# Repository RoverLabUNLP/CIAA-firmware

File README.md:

# EDU-CIAA-NXP con VS Code

Proyecto C para la EDU-CIAA-NXP (LPC4337, Cortex-M4), con sAPI y FreeRTOS.
Reutiliza GCC ARM 8.2.1 y las bibliotecas de CIAA Software 1.1 instalados
en este equipo. No requiere abrir Eclipse.

## Compilar

1. Abrir esta carpeta en VS Code.
2. Instalar la extensión recomendada **C/C++ de Microsoft**.
3. Comenzar por `app/src/main.c` y seguir la [guía de la aplicación RTOS](app/README.md).
4. Presionar **Ctrl+Shift+B** para ejecutar **CIAA: compilar**.

También se puede ejecutar `make` en la terminal de esta carpeta.
El esquema crea seis tareas. La tarea de estado alterna LEDB cada 500 ms;
las mediciones permanecen inválidas y las salidas propuestas en cero.
No se acciona ningún motor ni se reciben comandos UART todavía.
La salida está en `app/out/app.elf`
y `app/out/app.bin`. Los errores aparecen en el panel Problemas.
Para eliminar los resultados: `make clean` o la tarea **CIAA: limpiar**.

Compilar comprueba sintaxis y enlace con las bibliotecas de la placa.
Para comprobar LEDs, entradas, comunicaciones y tiempos hay que cargar el
programa en la EDU-CIAA y probarlo allí. Esta configuración no simula la placa.

## Herramientas y bibliotecas

Se usa `$HOME/CIAA_Software_1.1-linux-x64`. Para otra ubicación:

```sh
make CIAA_SDK_DIR=/ruta/a/CIAA_Software_1.1-linux-x64
```

También hay que actualizar `compilerPath` en `.vscode/c_cpp_properties.json`
si se cambia esa ubicación.

`tools/configure.sh` crea los enlaces locales `libs` y `scripts` al paquete.
No modifica la instalación original. El Makefile utiliza el sistema de
compilación `firmware_v3` distribuido en ese paquete. `app/config.mk`
selecciona sAPI, LPCOpen y FreeRTOS con `heap_4`. Las bibliotecas conservan sus licencias
en la instalación de CIAA Software.

El [manual de CIAA](https://www.proyecto-ciaa.com.ar/devwiki/doku.php%3Fid%3Ddesarrollo%3Afirmware%3Auser_manual.html)
describe Make, VS Code y OpenOCD. Sus ejemplos de firmware v1 usan OSEK/POSIX
y tienen una API diferente de sAPI: no se pueden copiar directamente a este
ejemplo. Aquí se usa el entorno sAPI que ya está instalado en este equipo.

La carga y depuración requieren conectar la placa y configurar el acceso USB.
Este proyecto prepara la compilación; todavía no se verificó su ejecución
sobre una placa física.

Al cambiar opciones de compilación en `app/config.mk`, ejecutar `make clean`
antes de volver a compilar para no reutilizar objetos de otra configuración.

Para el detalle del entorno y las instrucciones de handoff para agentes con
VSCode CIAA Bridge, consultar [docs-for-vscode-ciaa-bridge](docs-for-vscode-ciaa-bridge/README.md).

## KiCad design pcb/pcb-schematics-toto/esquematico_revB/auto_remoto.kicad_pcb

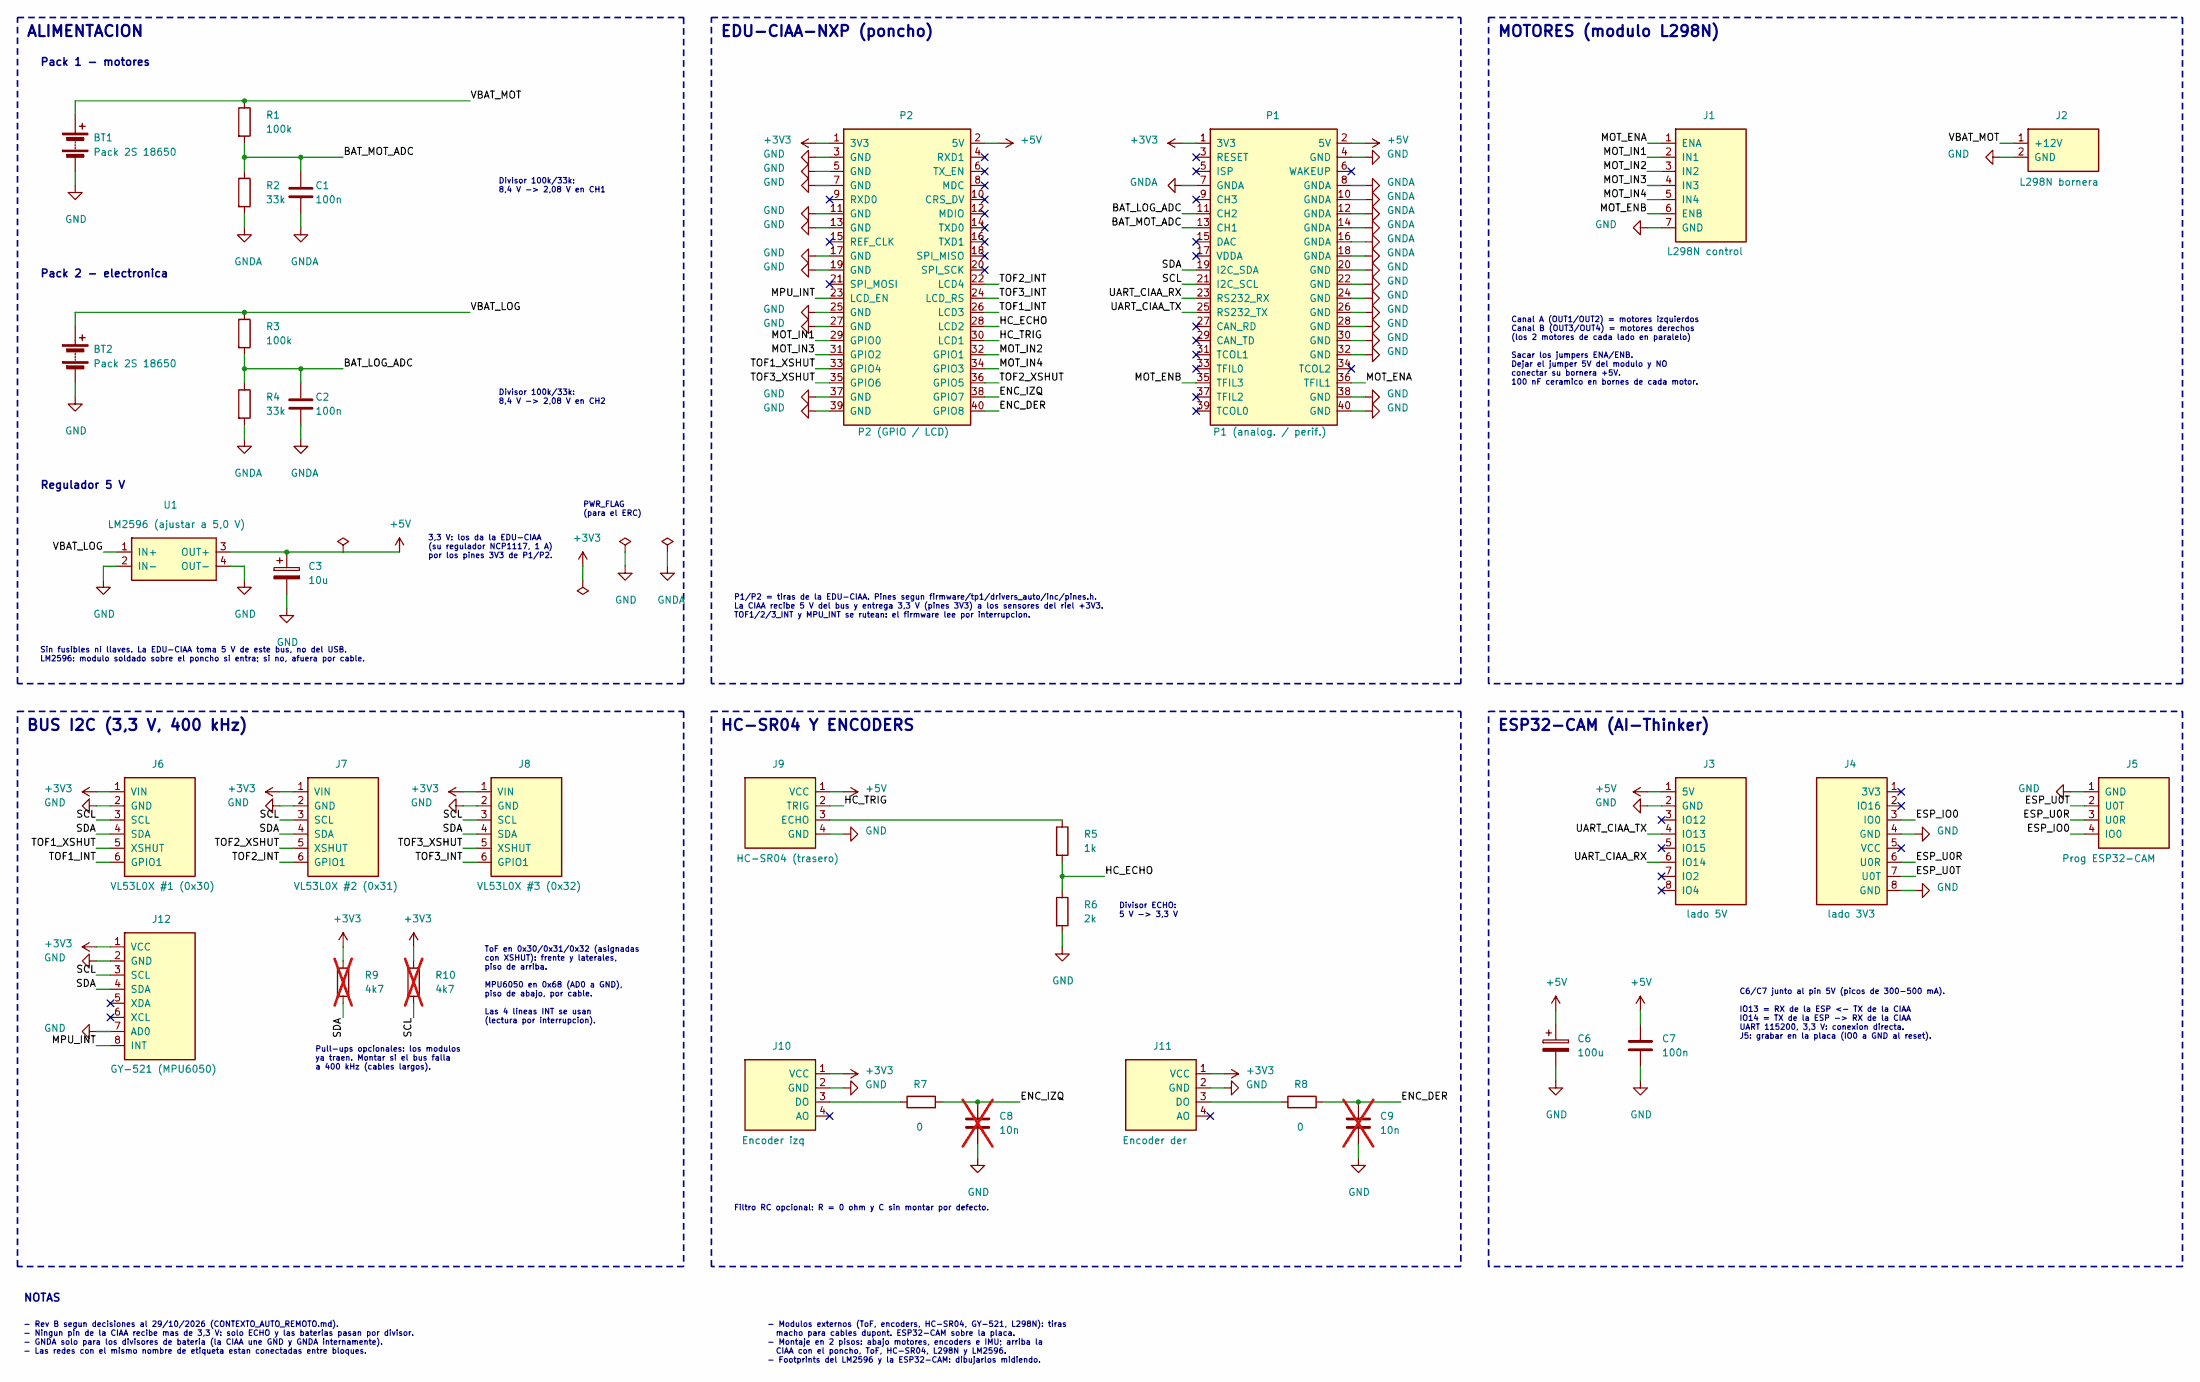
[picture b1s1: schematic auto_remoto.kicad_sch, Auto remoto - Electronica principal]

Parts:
BT1, BT2: Pack 2S 18650; Bornera_2_P5.00
C1, C2, C7: 100n; C_P5.00
C3: 10u; CP_D6.3_P2.50
C6: 100u; CP_D6.3_P2.50
C8, C9: 10n; C_P5.00; not fitted
J1: L298N control; Tira_1x07
J2: L298N bornera; Bornera_2_P5.00
J3: lado 5V; Zocalo_1x08
J4: lado 3V3; Zocalo_1x08
J5: Prog ESP32-CAM; Tira_1x04
J6: VL53L0X #1 (0x30); Tira_1x06
J7: VL53L0X #2 (0x31); Tira_1x06
J8: VL53L0X #3 (0x32); Tira_1x06
J9: HC-SR04 (trasero); Tira_1x04
J10: Encoder izq; Tira_1x04
J11: Encoder der; Tira_1x04
J12: GY-521 (MPU6050); Tira_1x08
P1: P1 (analog. / perif.); Tira_2x20_CIAA
P2: P2 (GPIO / LCD); Tira_2x20_CIAA
R1, R3: 100k; R_P10.16
R2, R4: 33k; R_P10.16
R5: 1k; R_P10.16
R6: 2k; R_P10.16
R7, R8: 0; R_P10.16
R9, R10: 4k7; R_P10.16; not fitted
U1: LM2596 (ajustar a 5,0 V); Modulo_LM2596

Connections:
+3V3: J6.1 (VIN), J7.1 (VIN), J8.1 (VIN), J10.1 (VCC), J11.1 (VCC), J12.1 (VCC), P1.1 (3V3), P2.1 (3V3), R9.1, R10.1
+5V: C3.1, C6.1, C7.1, J3.1 (5V), J9.1 (VCC), P1.2 (5V), P2.2 (5V), U1.3 (OUT+)
/BAT_LOG_ADC: C2.1, P1.11 (CH2), R3.2, R4.1
/BAT_MOT_ADC: C1.1, P1.13 (CH1), R1.2, R2.1
/ENC_DER: C9.1, P2.40 (GPIO8), R8.2
/ENC_IZQ: C8.1, P2.38 (GPIO7), R7.2
/ESP_IO0: J4.3 (IO0), J5.4 (IO0)
/ESP_U0R: J4.6 (U0R), J5.3 (U0R)
/ESP_U0T: J4.7 (U0T), J5.2 (U0T)
/HC_ECHO: P2.28 (LCD2), R5.2, R6.1
/HC_TRIG: J9.2 (TRIG), P2.30 (LCD1)
/MOT_ENA: J1.1 (ENA), P1.36 (TFIL1)
/MOT_ENB: J1.6 (ENB), P1.35 (TFIL3)
/MOT_IN1: J1.2 (IN1), P2.29 (GPIO0)
/MOT_IN2: J1.3 (IN2), P2.32 (GPIO1)
/MOT_IN3: J1.4 (IN3), P2.31 (GPIO2)
/MOT_IN4: J1.5 (IN4), P2.34 (GPIO3)
/MPU_INT: J12.8 (INT), P2.23 (LCD_EN)
/SCL: J6.3 (SCL), J7.3 (SCL), J8.3 (SCL), J12.3 (SCL), P1.21 (I2C_SCL), R10.2
/SDA: J6.4 (SDA), J7.4 (SDA), J8.4 (SDA), J12.4 (SDA), P1.19 (I2C_SDA), R9.2
/TOF1_INT: J6.6 (GPIO1), P2.26 (LCD3)
/TOF1_XSHUT: J6.5 (XSHUT), P2.33 (GPIO4)
/TOF2_INT: J7.6 (GPIO1), P2.22 (LCD4)
/TOF2_XSHUT: J7.5 (XSHUT), P2.36 (GPIO5)
/TOF3_INT: J8.6 (GPIO1), P2.24 (LCD_RS)
/TOF3_XSHUT: J8.5 (XSHUT), P2.35 (GPIO6)
/UART_CIAA_RX: J3.6 (IO14), P1.23 (RS232_RX)
/UART_CIAA_TX: J3.4 (IO13), P1.25 (RS232_TX)
/VBAT_LOG: BT2.1 (+), R3.1, U1.1 (IN+)
/VBAT_MOT: BT1.1 (+), J2.1 (+12V), R1.1
GND: BT1.2 (-), BT2.2 (-), C3.2, C6.2, C7.2, C8.2, C9.2, J1.7 (GND), J2.2 (GND), J3.2 (GND), J4.4 (GND), J4.8 (GND), J5.1 (GND), J6.2 (GND), J7.2 (GND), J8.2 (GND), J9.4 (GND), J10.2 (GND), J11.2 (GND), J12.2 (GND), J12.7 (AD0), P1.4 (GND), P1.20 (GND), P1.22 (GND), P1.24 (GND), P1.26 (GND), P1.28 (GND), P1.30 (GND), P1.32 (GND), P1.38 (GND), P1.40 (GND), P2.3 (GND), P2.5 (GND), P2.7 (GND), P2.11 (GND), P2.13 (GND), P2.17 (GND), P2.19 (GND), P2.25 (GND), P2.27 (GND), P2.37 (GND), P2.39 (GND), R6.2, U1.2 (IN-), U1.4 (OUT-)
GNDA: C1.2, C2.2, P1.7 (GNDA), P1.8 (GNDA), P1.10 (GNDA), P1.12 (GNDA), P1.14 (GNDA), P1.16 (GNDA), P1.18 (GNDA), R2.2, R4.2
unnamed: J9.3 (ECHO), R5.1
unnamed: J10.3 (DO), R7.1
unnamed: J11.3 (DO), R8.1

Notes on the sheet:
Regulador 5 V
Filtro RC opcional: R = 0 ohm y C sin montar por defecto.
MOTORES (modulo L298N)
Pack 2 - electronica
ESP32-CAM (AI-Thinker)
HC-SR04 Y ENCODERS
Divisor 100k/33k: 8,4 V -> 2,08 V en CH1
PWR_FLAG (para el ERC)
Sin fusibles ni llaves. La EDU-CIAA toma 5 V de este bus, no del USB. LM2596: modulo soldado sobre el poncho si entra; si no, afuera por cable.
BUS I2C (3,3 V, 400 kHz)
Pack 1 - motores
3,3 V: los da la EDU-CIAA (su regulador NCP1117, 1 A) por los pines 3V3 de P1/P2.
C6/C7 junto al pin 5V (picos de 300-500 mA). IO13 = RX de la ESP <- TX de la CIAA IO14 = TX de la ESP -> RX de la CIAA UART 115200, 3,3 V: conexion directa. J5: grabar en la placa (IO0 a GND al reset).
EDU-CIAA-NXP (poncho)
- Rev B segun decisiones al 29/10/2026 (CONTEXTO_AUTO_REMOTO.md). - Ningun pin de la CIAA recibe mas de 3,3 V: solo ECHO y las baterias pasan por divisor. - GNDA solo para los divisores de bateria (la CIAA une GND y GNDA internamente). - Las redes con el mismo nombre de etiqueta estan conectadas en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
NOTAS
ALIMENTACION
Divisor ECHO: 5 V -> 3,3 V
P1/P2 = tiras de la EDU-CIAA. Pines segun firmware/tp1/drivers_auto/inc/pines.h. La CIAA recibe 5 V del bus y entrega 3,3 V (pines 3V3) a los sensores del riel +3V3. TOF1/2/3_INT y MPU_INT se rutean: el firmware lee por interrupcion.
- Modulos externos (ToF, encoders, HC-SR04, GY-521, L298N): tiras macho para cables dupont. ESP32-CAM sobre la placa. - Montaje en 2 pisos: abajo motores, encoders e IMU; arriba la CIAA con el poncho, ToF, HC-SR04, L298N y LM2596. - Footprints del LM2596 y la ESP32-CAM: dibujarlos midiendo.
Divisor 100k/33k: 8,4 V -> 2,08 V en CH2
Canal A (OUT1/OUT2) = motores izquierdos Canal B (OUT3/OUT4) = motores derechos (los 2 motores de cada lado en paralelo) Sacar los jumpers ENA/ENB. Dejar el jumper 5V del modulo y NO conectar su bornera +5V. 100 nF ceramico en bornes de cada motor.
Pull-ups opcionales: los modulos ya traen. Montar si el bus falla a 400 kHz (cables largos).
ToF en 0x30/0x31/0x32 (asignadas con XSHUT): frente y laterales, piso de arriba. MPU6050 en 0x68 (AD0 a GND), piso de abajo, por cable. Las 4 lineas INT se usan (lectura por interrupcion).

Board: 2 copper layers, 38 parts (0 on the bottom side), 35 nets, no tracks yet.

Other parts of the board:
H1, H2, H3, H4: M3; Agujero_M3
